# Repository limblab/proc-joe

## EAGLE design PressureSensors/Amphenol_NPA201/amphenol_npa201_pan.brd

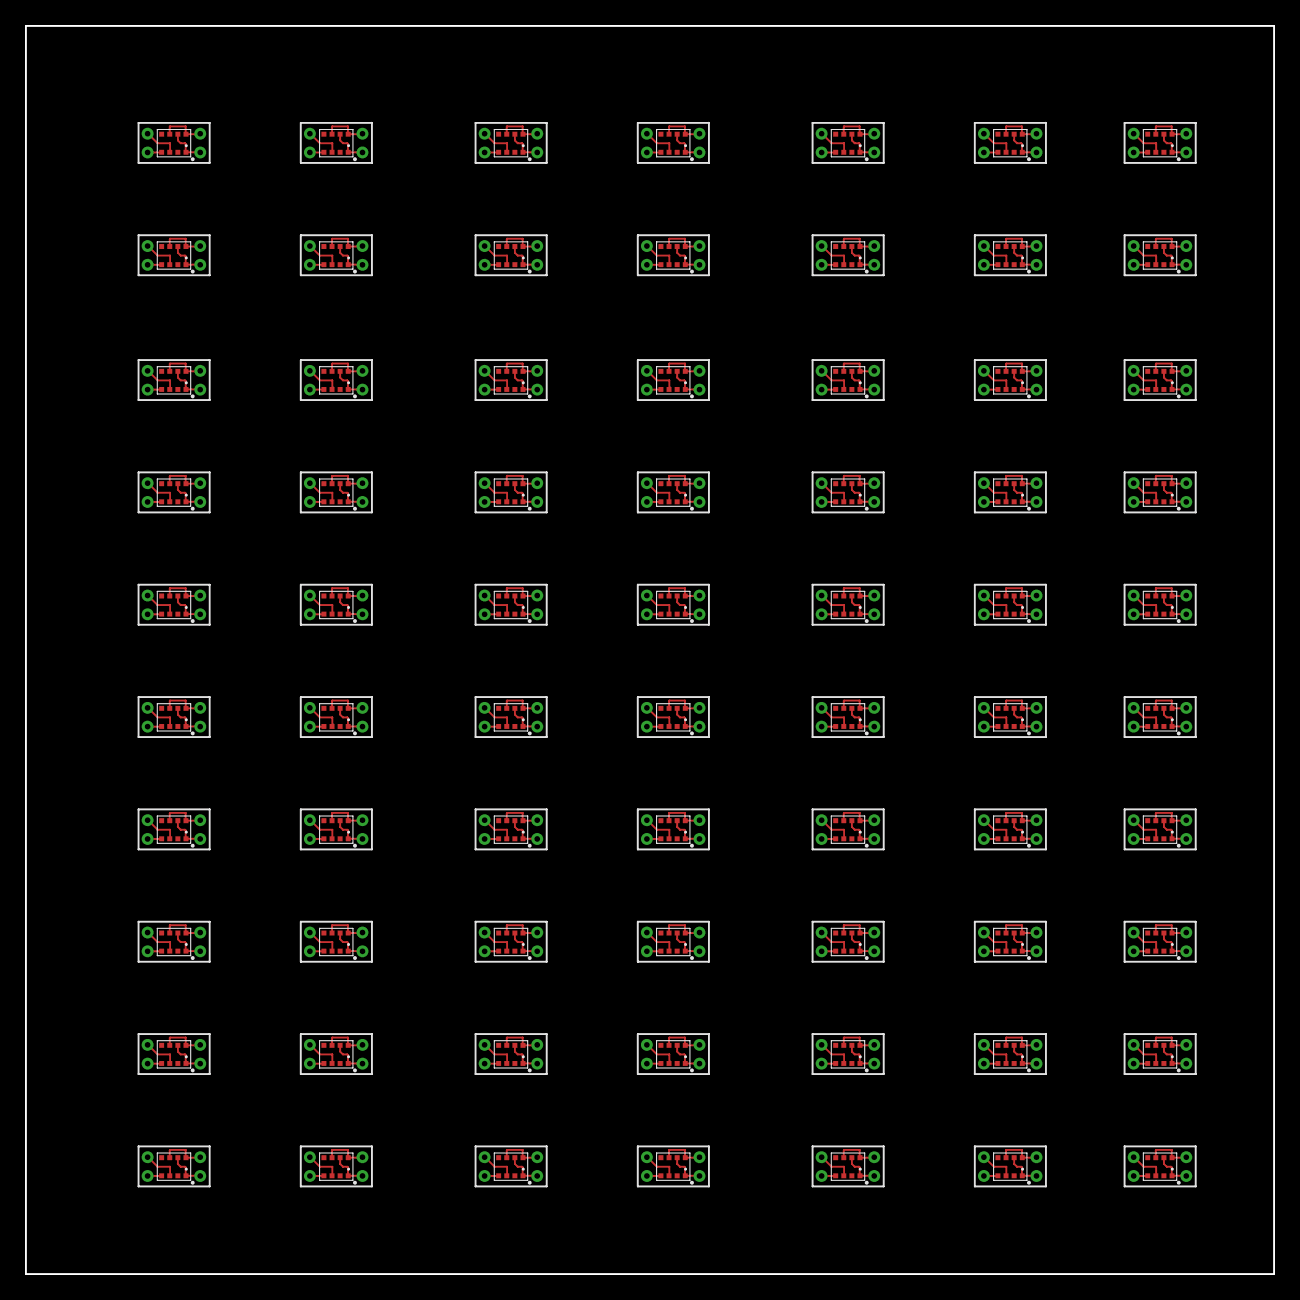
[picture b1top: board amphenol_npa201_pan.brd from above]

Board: 2 copper layers, 100.0 x 100.0 mm, 350 parts (0 on the bottom side), 280 nets.

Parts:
U$1, U$10, U$15, U$20, U$25, U$30, U$35, U$40, U$45, U$50, U$55, U$60, U$65, U$70, U$75, U$80, U$85, U$90, U$95, U$100, U$105, U$110, U$115, U$120, U$125, U$130, U$135, U$140, U$145, U$150, U$155, U$160, U$165, U$170, U$175, U$180, U$185, U$190, U$195, U$200, U$205, U$210, U$215, U$220, U$225, U$230, U$235, U$240, U$245, U$250, U$255, U$260, U$265, U$270, U$275, U$280, U$285, U$290, U$295, U$300, U$305, U$310, U$315, U$320, U$325, U$330, U$335, U$340, U$345, U$350: AMPHENOL_NPA201
U$2, U$3, U$4, U$5, U$6, U$7, U$8, U$9, U$11, U$12, U$13, U$14, U$16, U$17, U$18, U$19, U$21, U$22, U$23, U$24, U$26, U$27, U$28, U$29, U$31, U$32, U$33, U$34, U$36, U$37, U$38, U$39, U$41, U$42, U$43, U$44, U$46, U$47, U$48, U$49, U$51, U$52, U$53, U$54, U$56, U$57, U$58, U$59, U$61, U$62, U$63, U$64, U$66, U$67, U$68, U$69, U$71, U$72, U$73, U$74, U$76, U$77, U$78, U$79, U$81, U$82, U$83, U$84, U$86, U$87, U$88, U$89, U$91, U$92, U$93, U$94, U$96, U$97, U$98, U$99, U$101, U$102, U$103, U$104, U$106, U$107, U$108, U$109, U$111, U$112, U$113, U$114, U$116, U$117, U$118, U$119, U$121, U$122, U$123, U$124, U$126, U$127, U$128, U$129, U$131, U$132, U$133, U$134, U$136, U$137, U$138, U$139, U$141, U$142, U$143, U$144, U$146, U$147, U$148, U$149, U$151, U$152, U$153, U$154, U$156, U$157, U$158, U$159, U$161, U$162, U$163, U$164, U$166, U$167, U$168, U$169, U$171, U$172, U$173, U$174, U$176, U$177, U$178, U$179, U$181, U$182, U$183, U$184, U$186, U$187, U$188, U$189, U$191, U$192, U$193, U$194, U$196, U$197, U$198, U$199, U$201, U$202, U$203, U$204, U$206, U$207, U$208, U$209, U$211, U$212, U$213, U$214, U$216, U$217, U$218, U$219, U$221, U$222, U$223, U$224, U$226, U$227, U$228, U$229, U$231, U$232, U$233, U$234, U$236, U$237, U$238, U$239, U$241, U$242, U$243, U$244, U$246, U$247, U$248, U$249, U$251, U$252, U$253, U$254, U$256, U$257, U$258, U$259, U$261, U$262, U$263, U$264, U$266, U$267, U$268, U$269, U$271, U$272, U$273, U$274, U$276, U$277, U$278, U$279, U$281, U$282, U$283, U$284, U$286, U$287, U$288, U$289, U$291, U$292, U$293, U$294, U$296, U$297, U$298, U$299, U$301, U$302, U$303, U$304, U$306, U$307, U$308, U$309, U$311, U$312, U$313, U$314, U$316, U$317, U$318, U$319, U$321, U$322, U$323, U$324, U$326, U$327, U$328, U$329, U$331, U$332, U$333, U$334, U$336, U$337, U$338, U$339, U$341, U$342, U$343, U$344, U$346, U$347, U$348, U$349: WIREPAD_0,8/0,45

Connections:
+3V1: U$8.P$1, U$10.P$6, U$10.P$8
+3V2: U$13.P$1, U$15.P$6, U$15.P$8
+3V3: U$1.P$6, U$1.P$8, U$4.P$1
+3V4: U$18.P$1, U$20.P$6, U$20.P$8
+3V5: U$23.P$1, U$25.P$6, U$25.P$8
+3V6: U$28.P$1, U$30.P$6, U$30.P$8
+3V7: U$33.P$1, U$35.P$6, U$35.P$8
+3V8: U$38.P$1, U$40.P$6, U$40.P$8
+3V9: U$43.P$1, U$45.P$6, U$45.P$8
+3V10: U$48.P$1, U$50.P$6, U$50.P$8
+3V11: U$53.P$1, U$55.P$6, U$55.P$8
+3V12: U$58.P$1, U$60.P$6, U$60.P$8
+3V13: U$63.P$1, U$65.P$6, U$65.P$8
+3V14: U$68.P$1, U$70.P$6, U$70.P$8
+3V15: U$73.P$1, U$75.P$6, U$75.P$8
+3V16: U$78.P$1, U$80.P$6, U$80.P$8
+3V17: U$83.P$1, U$85.P$6, U$85.P$8
+3V18: U$88.P$1, U$90.P$6, U$90.P$8
+3V19: U$93.P$1, U$95.P$6, U$95.P$8
+3V20: U$98.P$1, U$100.P$6, U$100.P$8
+3V21: U$103.P$1, U$105.P$6, U$105.P$8
+3V22: U$108.P$1, U$110.P$6, U$110.P$8
+3V23: U$113.P$1, U$115.P$6, U$115.P$8
+3V24: U$118.P$1, U$120.P$6, U$120.P$8
+3V25: U$123.P$1, U$125.P$6, U$125.P$8
+3V26: U$128.P$1, U$130.P$6, U$130.P$8
+3V27: U$133.P$1, U$135.P$6, U$135.P$8
+3V28: U$138.P$1, U$140.P$6, U$140.P$8
+3V29: U$143.P$1, U$145.P$6, U$145.P$8
+3V30: U$148.P$1, U$150.P$6, U$150.P$8
+3V31: U$153.P$1, U$155.P$6, U$155.P$8
+3V32: U$158.P$1, U$160.P$6, U$160.P$8
+3V33: U$163.P$1, U$165.P$6, U$165.P$8
+3V34: U$168.P$1, U$170.P$6, U$170.P$8
+3V35: U$173.P$1, U$175.P$6, U$175.P$8
+3V36: U$178.P$1, U$180.P$6, U$180.P$8
+3V37: U$183.P$1, U$185.P$6, U$185.P$8
+3V38: U$188.P$1, U$190.P$6, U$190.P$8
+3V39: U$193.P$1, U$195.P$6, U$195.P$8
+3V40: U$198.P$1, U$200.P$6, U$200.P$8
+3V41: U$203.P$1, U$205.P$6, U$205.P$8
+3V42: U$208.P$1, U$210.P$6, U$210.P$8
+3V43: U$213.P$1, U$215.P$6, U$215.P$8
+3V44: U$218.P$1, U$220.P$6, U$220.P$8
+3V45: U$223.P$1, U$225.P$6, U$225.P$8
+3V46: U$228.P$1, U$230.P$6, U$230.P$8
+3V47: U$233.P$1, U$235.P$6, U$235.P$8
+3V48: U$238.P$1, U$240.P$6, U$240.P$8
+3V49: U$243.P$1, U$245.P$6, U$245.P$8
+3V50: U$248.P$1, U$250.P$6, U$250.P$8
+3V51: U$253.P$1, U$255.P$6, U$255.P$8
+3V52: U$258.P$1, U$260.P$6, U$260.P$8
+3V53: U$263.P$1, U$265.P$6, U$265.P$8
+3V54: U$268.P$1, U$270.P$6, U$270.P$8
+3V55: U$273.P$1, U$275.P$6, U$275.P$8
+3V56: U$278.P$1, U$280.P$6, U$280.P$8
+3V57: U$283.P$1, U$285.P$6, U$285.P$8
+3V58: U$288.P$1, U$290.P$6, U$290.P$8
+3V59: U$293.P$1, U$295.P$6, U$295.P$8
+3V60: U$298.P$1, U$300.P$6, U$300.P$8
+3V61: U$303.P$1, U$305.P$6, U$305.P$8
+3V62: U$308.P$1, U$310.P$6, U$310.P$8
+3V63: U$313.P$1, U$315.P$6, U$315.P$8
+3V64: U$318.P$1, U$320.P$6, U$320.P$8
+3V65: U$323.P$1, U$325.P$6, U$325.P$8
+3V66: U$328.P$1, U$330.P$6, U$330.P$8
+3V67: U$333.P$1, U$335.P$6, U$335.P$8
+3V68: U$338.P$1, U$340.P$6, U$340.P$8
+3V69: U$343.P$1, U$345.P$6, U$345.P$8
+3V70: U$348.P$1, U$350.P$6, U$350.P$8
GND: U$1.P$1, U$1.P$7, U$5.P$1
GND1: U$9.P$1, U$10.P$1, U$10.P$7
GND2: U$14.P$1, U$15.P$1, U$15.P$7
GND3: U$19.P$1, U$20.P$1, U$20.P$7
GND4: U$24.P$1, U$25.P$1, U$25.P$7
GND5: U$29.P$1, U$30.P$1, U$30.P$7
GND6: U$34.P$1, U$35.P$1, U$35.P$7
GND7: U$39.P$1, U$40.P$1, U$40.P$7
GND8: U$44.P$1, U$45.P$1, U$45.P$7
GND9: U$49.P$1, U$50.P$1, U$50.P$7
GND10: U$54.P$1, U$55.P$1, U$55.P$7
GND11: U$59.P$1, U$60.P$1, U$60.P$7
GND12: U$64.P$1, U$65.P$1, U$65.P$7
GND13: U$69.P$1, U$70.P$1, U$70.P$7
GND14: U$74.P$1, U$75.P$1, U$75.P$7
GND15: U$79.P$1, U$80.P$1, U$80.P$7
GND16: U$84.P$1, U$85.P$1, U$85.P$7
GND17: U$89.P$1, U$90.P$1, U$90.P$7
GND18: U$94.P$1, U$95.P$1, U$95.P$7
GND19: U$99.P$1, U$100.P$1, U$100.P$7
GND20: U$104.P$1, U$105.P$1, U$105.P$7
GND21: U$109.P$1, U$110.P$1, U$110.P$7
GND22: U$114.P$1, U$115.P$1, U$115.P$7
GND23: U$119.P$1, U$120.P$1, U$120.P$7
GND24: U$124.P$1, U$125.P$1, U$125.P$7
GND25: U$129.P$1, U$130.P$1, U$130.P$7
GND26: U$134.P$1, U$135.P$1, U$135.P$7
GND27: U$139.P$1, U$140.P$1, U$140.P$7
GND28: U$144.P$1, U$145.P$1, U$145.P$7
GND29: U$149.P$1, U$150.P$1, U$150.P$7
GND30: U$154.P$1, U$155.P$1, U$155.P$7
GND31: U$159.P$1, U$160.P$1, U$160.P$7
GND32: U$164.P$1, U$165.P$1, U$165.P$7
GND33: U$169.P$1, U$170.P$1, U$170.P$7
GND34: U$174.P$1, U$175.P$1, U$175.P$7
GND35: U$179.P$1, U$180.P$1, U$180.P$7
GND36: U$184.P$1, U$185.P$1, U$185.P$7
GND37: U$189.P$1, U$190.P$1, U$190.P$7
GND38: U$194.P$1, U$195.P$1, U$195.P$7
GND39: U$199.P$1, U$200.P$1, U$200.P$7
GND40: U$204.P$1, U$205.P$1, U$205.P$7
GND41: U$209.P$1, U$210.P$1, U$210.P$7
GND42: U$214.P$1, U$215.P$1, U$215.P$7
GND43: U$219.P$1, U$220.P$1, U$220.P$7
GND44: U$224.P$1, U$225.P$1, U$225.P$7
GND45: U$229.P$1, U$230.P$1, U$230.P$7
GND46: U$234.P$1, U$235.P$1, U$235.P$7
GND47: U$239.P$1, U$240.P$1, U$240.P$7
GND48: U$244.P$1, U$245.P$1, U$245.P$7
GND49: U$249.P$1, U$250.P$1, U$250.P$7
GND50: U$254.P$1, U$255.P$1, U$255.P$7
GND51: U$259.P$1, U$260.P$1, U$260.P$7
GND52: U$264.P$1, U$265.P$1, U$265.P$7
GND53: U$269.P$1, U$270.P$1, U$270.P$7
GND54: U$274.P$1, U$275.P$1, U$275.P$7
GND55: U$279.P$1, U$280.P$1, U$280.P$7
GND56: U$284.P$1, U$285.P$1, U$285.P$7
GND57: U$289.P$1, U$290.P$1, U$290.P$7
GND58: U$294.P$1, U$295.P$1, U$295.P$7
GND59: U$299.P$1, U$300.P$1, U$300.P$7
GND60: U$304.P$1, U$305.P$1, U$305.P$7
GND61: U$309.P$1, U$310.P$1, U$310.P$7
GND62: U$314.P$1, U$315.P$1, U$315.P$7
GND63: U$319.P$1, U$320.P$1, U$320.P$7
GND64: U$324.P$1, U$325.P$1, U$325.P$7
GND65: U$329.P$1, U$330.P$1, U$330.P$7
GND66: U$334.P$1, U$335.P$1, U$335.P$7
GND67: U$339.P$1, U$340.P$1, U$340.P$7
GND68: U$344.P$1, U$345.P$1, U$345.P$7
GND69: U$349.P$1, U$350.P$1, U$350.P$7
unnamed: U$1.P$3, U$2.P$1
unnamed: U$1.P$4, U$3.P$1
unnamed: U$6.P$1, U$10.P$3
unnamed: U$7.P$1, U$10.P$4
unnamed: U$11.P$1, U$15.P$3
unnamed: U$12.P$1, U$15.P$4
unnamed: U$16.P$1, U$20.P$3
unnamed: U$17.P$1, U$20.P$4
unnamed: U$21.P$1, U$25.P$3
unnamed: U$22.P$1, U$25.P$4
unnamed: U$26.P$1, U$30.P$3
unnamed: U$27.P$1, U$30.P$4
unnamed: U$31.P$1, U$35.P$3
unnamed: U$32.P$1, U$35.P$4
unnamed: U$36.P$1, U$40.P$3
unnamed: U$37.P$1, U$40.P$4
unnamed: U$41.P$1, U$45.P$3
unnamed: U$42.P$1, U$45.P$4
unnamed: U$46.P$1, U$50.P$3
unnamed: U$47.P$1, U$50.P$4
unnamed: U$51.P$1, U$55.P$3
unnamed: U$52.P$1, U$55.P$4
unnamed: U$56.P$1, U$60.P$3
unnamed: U$57.P$1, U$60.P$4
unnamed: U$61.P$1, U$65.P$3
unnamed: U$62.P$1, U$65.P$4
unnamed: U$66.P$1, U$70.P$3
unnamed: U$67.P$1, U$70.P$4
unnamed: U$71.P$1, U$75.P$3
unnamed: U$72.P$1, U$75.P$4
unnamed: U$76.P$1, U$80.P$3
unnamed: U$77.P$1, U$80.P$4
unnamed: U$81.P$1, U$85.P$3
unnamed: U$82.P$1, U$85.P$4
unnamed: U$86.P$1, U$90.P$3
unnamed: U$87.P$1, U$90.P$4
unnamed: U$91.P$1, U$95.P$3
unnamed: U$92.P$1, U$95.P$4
unnamed: U$96.P$1, U$100.P$3
unnamed: U$97.P$1, U$100.P$4
unnamed: U$101.P$1, U$105.P$3
unnamed: U$102.P$1, U$105.P$4
unnamed: U$106.P$1, U$110.P$3
unnamed: U$107.P$1, U$110.P$4
unnamed: U$111.P$1, U$115.P$3
unnamed: U$112.P$1, U$115.P$4
unnamed: U$116.P$1, U$120.P$3
unnamed: U$117.P$1, U$120.P$4
unnamed: U$121.P$1, U$125.P$3
unnamed: U$122.P$1, U$125.P$4
unnamed: U$126.P$1, U$130.P$3
unnamed: U$127.P$1, U$130.P$4
unnamed: U$131.P$1, U$135.P$3
unnamed: U$132.P$1, U$135.P$4
unnamed: U$136.P$1, U$140.P$3
unnamed: U$137.P$1, U$140.P$4
unnamed: U$141.P$1, U$145.P$3
unnamed: U$142.P$1, U$145.P$4
unnamed: U$146.P$1, U$150.P$3
unnamed: U$147.P$1, U$150.P$4
unnamed: U$151.P$1, U$155.P$3
unnamed: U$152.P$1, U$155.P$4
unnamed: U$156.P$1, U$160.P$3
unnamed: U$157.P$1, U$160.P$4
unnamed: U$161.P$1, U$165.P$3
unnamed: U$162.P$1, U$165.P$4
unnamed: U$166.P$1, U$170.P$3
unnamed: U$167.P$1, U$170.P$4
unnamed: U$171.P$1, U$175.P$3
unnamed: U$172.P$1, U$175.P$4
unnamed: U$176.P$1, U$180.P$3
unnamed: U$177.P$1, U$180.P$4
unnamed: U$181.P$1, U$185.P$3
unnamed: U$182.P$1, U$185.P$4
unnamed: U$186.P$1, U$190.P$3
unnamed: U$187.P$1, U$190.P$4
unnamed: U$191.P$1, U$195.P$3
unnamed: U$192.P$1, U$195.P$4
unnamed: U$196.P$1, U$200.P$3
unnamed: U$197.P$1, U$200.P$4
unnamed: U$201.P$1, U$205.P$3
unnamed: U$202.P$1, U$205.P$4
unnamed: U$206.P$1, U$210.P$3
unnamed: U$207.P$1, U$210.P$4
unnamed: U$211.P$1, U$215.P$3
unnamed: U$212.P$1, U$215.P$4
unnamed: U$216.P$1, U$220.P$3
unnamed: U$217.P$1, U$220.P$4
unnamed: U$221.P$1, U$225.P$3
unnamed: U$222.P$1, U$225.P$4
unnamed: U$226.P$1, U$230.P$3
unnamed: U$227.P$1, U$230.P$4
unnamed: U$231.P$1, U$235.P$3
unnamed: U$232.P$1, U$235.P$4
unnamed: U$236.P$1, U$240.P$3
unnamed: U$237.P$1, U$240.P$4
unnamed: U$241.P$1, U$245.P$3
unnamed: U$242.P$1, U$245.P$4
unnamed: U$246.P$1, U$250.P$3
unnamed: U$247.P$1, U$250.P$4
unnamed: U$251.P$1, U$255.P$3
unnamed: U$252.P$1, U$255.P$4
unnamed: U$256.P$1, U$260.P$3
unnamed: U$257.P$1, U$260.P$4
unnamed: U$261.P$1, U$265.P$3
unnamed: U$262.P$1, U$265.P$4
unnamed: U$266.P$1, U$270.P$3
unnamed: U$267.P$1, U$270.P$4
unnamed: U$271.P$1, U$275.P$3
unnamed: U$272.P$1, U$275.P$4
unnamed: U$276.P$1, U$280.P$3
unnamed: U$277.P$1, U$280.P$4
unnamed: U$281.P$1, U$285.P$3
unnamed: U$282.P$1, U$285.P$4
unnamed: U$286.P$1, U$290.P$3
unnamed: U$287.P$1, U$290.P$4
unnamed: U$291.P$1, U$295.P$3
unnamed: U$292.P$1, U$295.P$4
unnamed: U$296.P$1, U$300.P$3
unnamed: U$297.P$1, U$300.P$4
unnamed: U$301.P$1, U$305.P$3
unnamed: U$302.P$1, U$305.P$4
unnamed: U$306.P$1, U$310.P$3
unnamed: U$307.P$1, U$310.P$4
unnamed: U$311.P$1, U$315.P$3
unnamed: U$312.P$1, U$315.P$4
unnamed: U$316.P$1, U$320.P$3
unnamed: U$317.P$1, U$320.P$4
unnamed: U$321.P$1, U$325.P$3
unnamed: U$322.P$1, U$325.P$4
unnamed: U$326.P$1, U$330.P$3
unnamed: U$327.P$1, U$330.P$4
unnamed: U$331.P$1, U$335.P$3
unnamed: U$332.P$1, U$335.P$4
unnamed: U$336.P$1, U$340.P$3
unnamed: U$337.P$1, U$340.P$4
unnamed: U$341.P$1, U$345.P$3
unnamed: U$342.P$1, U$345.P$4
unnamed: U$346.P$1, U$350.P$3
unnamed: U$347.P$1, U$350.P$4
